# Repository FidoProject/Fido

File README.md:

# Creative Cloud for PlayOnLinux

**This script currently does not work, see [issue #52](https://github.com/corbindavenport/creative-cloud-linux/issues/52) for more details.**

This is an install script for [Adobe Creative Cloud](https://www.adobe.com/creativecloud.html), designed to be used with [PlayOnLinux](https://www.playonlinux.com). The script sets up the Adobe Creative Cloud desktop program, which can be used to install and update Photoshop, Lightroom, Dreamweaver, Illustrator, and other apps.

Only Photoshop CC, Bridge CC, Lightroom 5, and the Creative Cloud manager have been extensively tested. The newest Lightroom CC app is not supported right now. File syncing currently [does not work](https://github.com/corbindavenport/creative-cloud-linux/issues/29).

A (free) Adobe ID is required. Most Adobe applications require [a paid subscription](https://www.adobe.com/creativecloud/plans.html).

## How to use this script

1. Download PlayOnLinux from your distribution's package manager (e.g. Ubuntu Software Center) or from [the PlayOnLinux website](https://www.playonlinux.com/en/download.html)
2. Save the [install script](https://raw.githubusercontent.com/corbindavenport/creative-cloud-linux/master/creativecloud.sh) to your computer
3. Open PlayOnLinux, go to Tools > Run a local script
4. Select the install script you just downloaded

After the setup process is finished, you can open `Adobe Creative Cloud` from PlayOnLinux to download and install the apps you need. After you download an app, you can add a PlayOnLinux shortcut for it by clicking Adobe Application Manager in the app list, clicking `Configure`, and clicking `Make a new shortcut from this virtual drive`. Then look for the app you need, like Photoshop.exe, and add it.

**Tip:** Tooltips in Photoshop might not disappear automatically. You can turn off tooltips completely by going to `Edit > Preferences > Tools` and un-checking the `Show tooltips` box.

If the installer crashes, see the [Troubleshooting page](https://github.com/corbindavenport/creative-cloud-linux/wiki/Troubleshooting). If you still have issues, try [the classic script](https://github.com/corbindavenport/creative-cloud-linux/tree/classic).

---------------------------------------

    This program is free software: you can redistribute it and/or modify
    it under the terms of the GNU General Public License as published by
    the Free Software Foundation, either version 3 of the License, or
    (at your option) any later version.

    This program is distributed in the hope that it will be useful,
    but WITHOUT ANY WARRANTY; without even the implied warranty of
    MERCHANTABILITY or FITNESS FOR A PARTICULAR PURPOSE.  See the
    GNU General Public License for more details.

    You should have received a copy of the GNU General Public License
    along with this program.  If not, see <http://www.gnu.org/licenses/>.

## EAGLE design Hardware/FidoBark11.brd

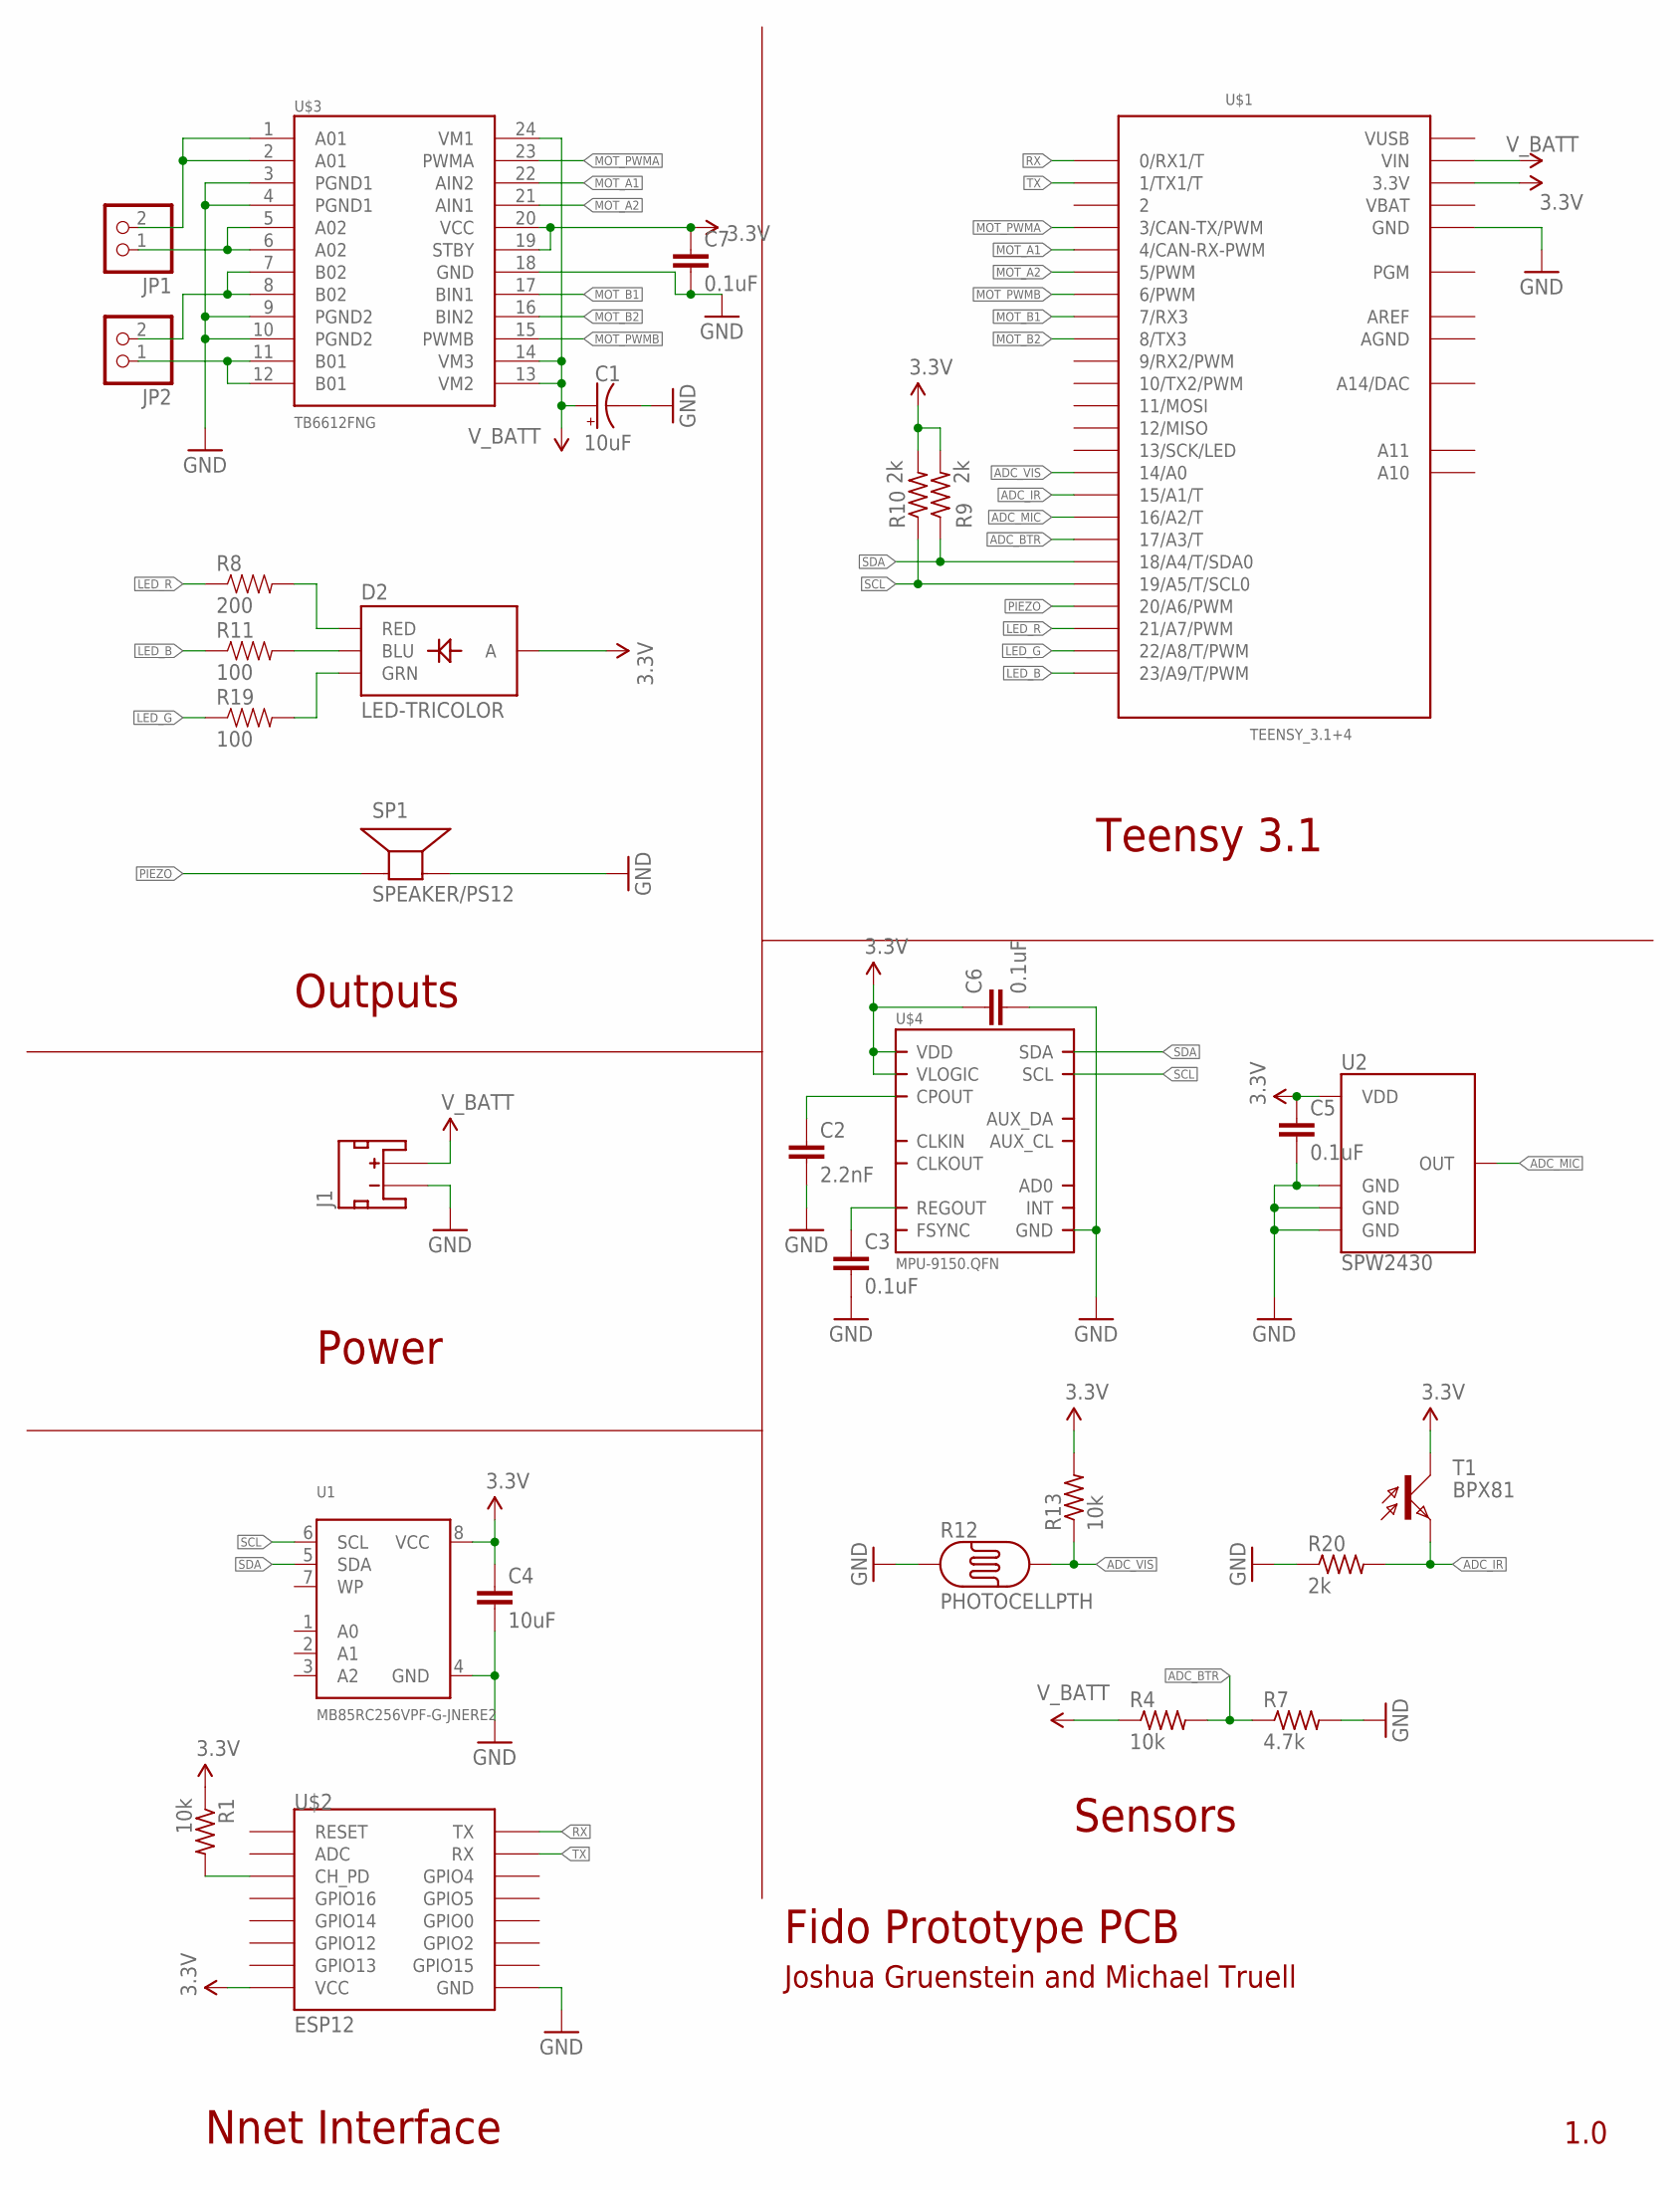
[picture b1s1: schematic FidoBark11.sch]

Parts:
C1: 10uF; EIA3216
C2: 2.2nF; C0603
C3, C5, C6, C7: 0.1uF; C0603
C4: 10uF; 0603-CAP
D2: LED-TRICOLOR; LED-TRICOLOR-SMD
J1: JST_2MM_MALE; JST-2-SMD
JP1, JP2: PINHD-1X2; 1X02
R1, R4, R13: 10k; R0603
R7: 4.7k; R0603
R8: 200; 0402-RES
R9, R10, R20: 2k; R0603
R11, R19: 100; 0402-RES
R12: PHOTOCELLPTH; PHOTOCELL
SP1: SPEAKER/PS12; PS12
T1: BPX81
U1: MB85RC256VPF-G-JNERE2; SOIC8_208MIL
U2: SPW2430; ADMP401
U$1: TEENSY_3.1+4
U$2: ESP12
U$3: TB6612FNG; SSOP24
U$4: MPU-9150.QFN; QFN.24.4X4

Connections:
3.3V: C4.1, C5.1, C6.1, C7.1, D2.A, R1.1, R9.2, R10.2, R13.2, T1.C, U1.8 (VCC), U2.5 (VDD), U$1.3.3V, U$1.3.3V1 (3.3V), U$2.VCC, U$3.19 (STBY), U$3.20 (VCC), U$4.3 (VDD), U$4.8 (VLOGIC), U$4.13 (VDD)
ADC_BTR: R4.2, R7.1, U$1.17/A3 (17/A3/T)
ADC_IR: R20.2, T1.E, U$1.15/A1 (15/A1/T)
ADC_MIC: U2.1 (OUT), U$1.16/A2 (16/A2/T)
ADC_VIS: R12.2, R13.1, U$1.14/A0
AGND: U$1.AGND
AREF: U$1.AREF
BLU: D2.B (BLU), R11.2
GND: C1.C (-), C2.2, C3.2, C4.2, C5.2, C6.2, C7.2, J1.1 (-), R7.2, R12.1, R20.1, SP1.P$2 (-), U1.4 (GND), U2.2 (GND), U2.4 (GND), U2.6 (GND), U$1.GND, U$1.GND1 (GND), U$2.GND, U$3.3 (PGND1), U$3.4 (PGND1), U$3.9 (PGND2), U$3.10 (PGND2), U$3.18 (GND), U$4.15 (GND), U$4.17 (GND), U$4.18 (GND)
GRN: D2.G (GRN), R19.2
LED_B: R11.1, U$1.23/A9 (23/A9/T/PWM)
LED_G: R19.1, U$1.22/A8 (22/A8/T/PWM)
LED_R: R8.1, U$1.21/A7 (21/A7/PWM)
MOT_A1: U$1.4 (4/CAN-RX-PWM), U$3.22 (AIN2)
MOT_A2: U$1.5 (5/PWM), U$3.21 (AIN1)
MOT_B1: U$1.7 (7/RX3), U$3.17 (BIN1)
MOT_B2: U$1.8 (8/TX3), U$3.16 (BIN2)
MOT_PWMA: U$1.3 (3/CAN-TX/PWM), U$3.23 (PWMA)
MOT_PWMB: U$1.6 (6/PWM), U$3.15 (PWMB)
unnamed: JP1.2, U$3.1 (A01), U$3.2 (A01)
unnamed: R1.2, U$2.CH_PD
unnamed: JP1.1, U$3.5 (A02), U$3.6 (A02)
unnamed: JP2.2, U$3.7 (B02), U$3.8 (B02)
unnamed: JP2.1, U$3.11 (B01), U$3.12 (B01)
unnamed: C3.1, U$4.10 (REGOUT)
unnamed: C2.1, U$4.20 (CPOUT)
PIEZO: SP1.P$1 (+), U$1.20/A6 (20/A6/PWM)
RED: D2.R (RED), R8.2
RX: U$1.0 (0/RX1/T), U$2.TX
SCL: R10.1, U1.6 (SCL), U$1.19/A5 (19/A5/T/SCL0), U$4.23 (SCL)
SDA: R9.1, U1.5 (SDA), U$1.18/A4 (18/A4/T/SDA0), U$4.24 (SDA)
TX: U$1.1 (1/TX1/T), U$2.RX
VBAT: U$1.VBAT
VUSB: U$1.VUSB
V_BATT: C1.A (+), J1.2 (+), R4.1, U$1.VIN, U$3.13 (VM2), U$3.14 (VM3), U$3.24 (VM1)

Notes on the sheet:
Sensors
Teensy 3.1
Fido Prototype PCB
Joshua Gruenstein and Michael Truell
1.0
Nnet Interface
Outputs
Power

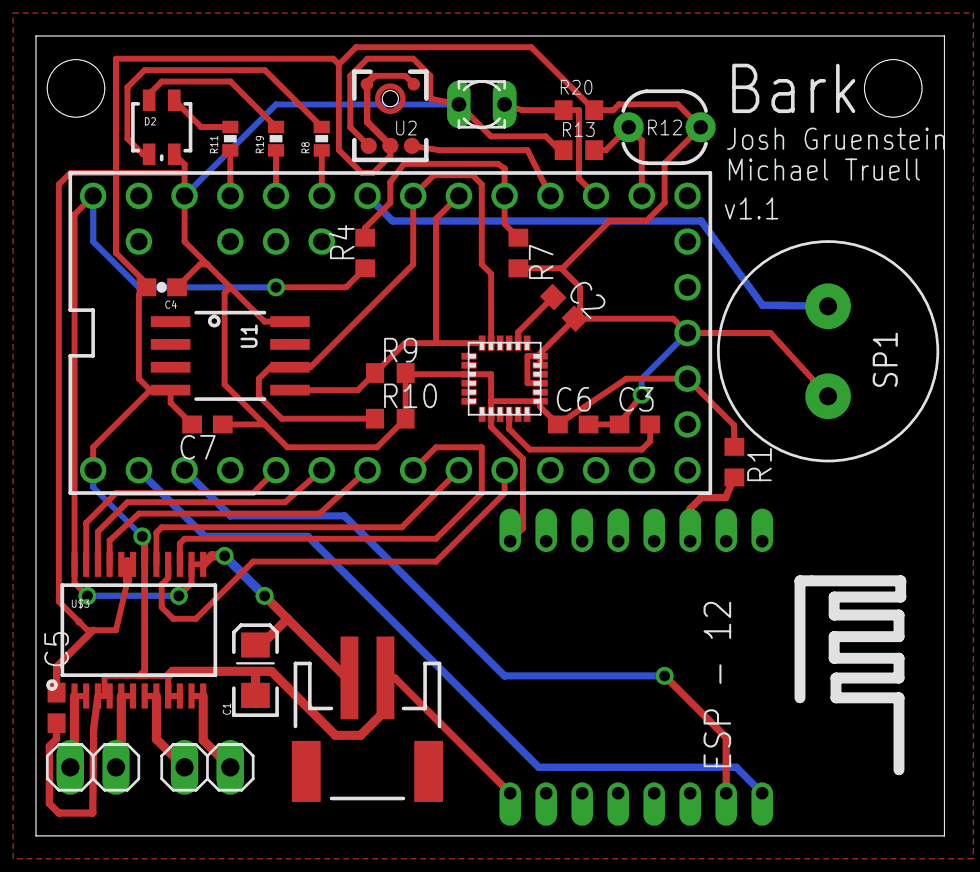
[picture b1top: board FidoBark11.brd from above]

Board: 2 copper layers, 50.5 x 44.4 mm, 30 parts (0 on the bottom side), 31 nets.

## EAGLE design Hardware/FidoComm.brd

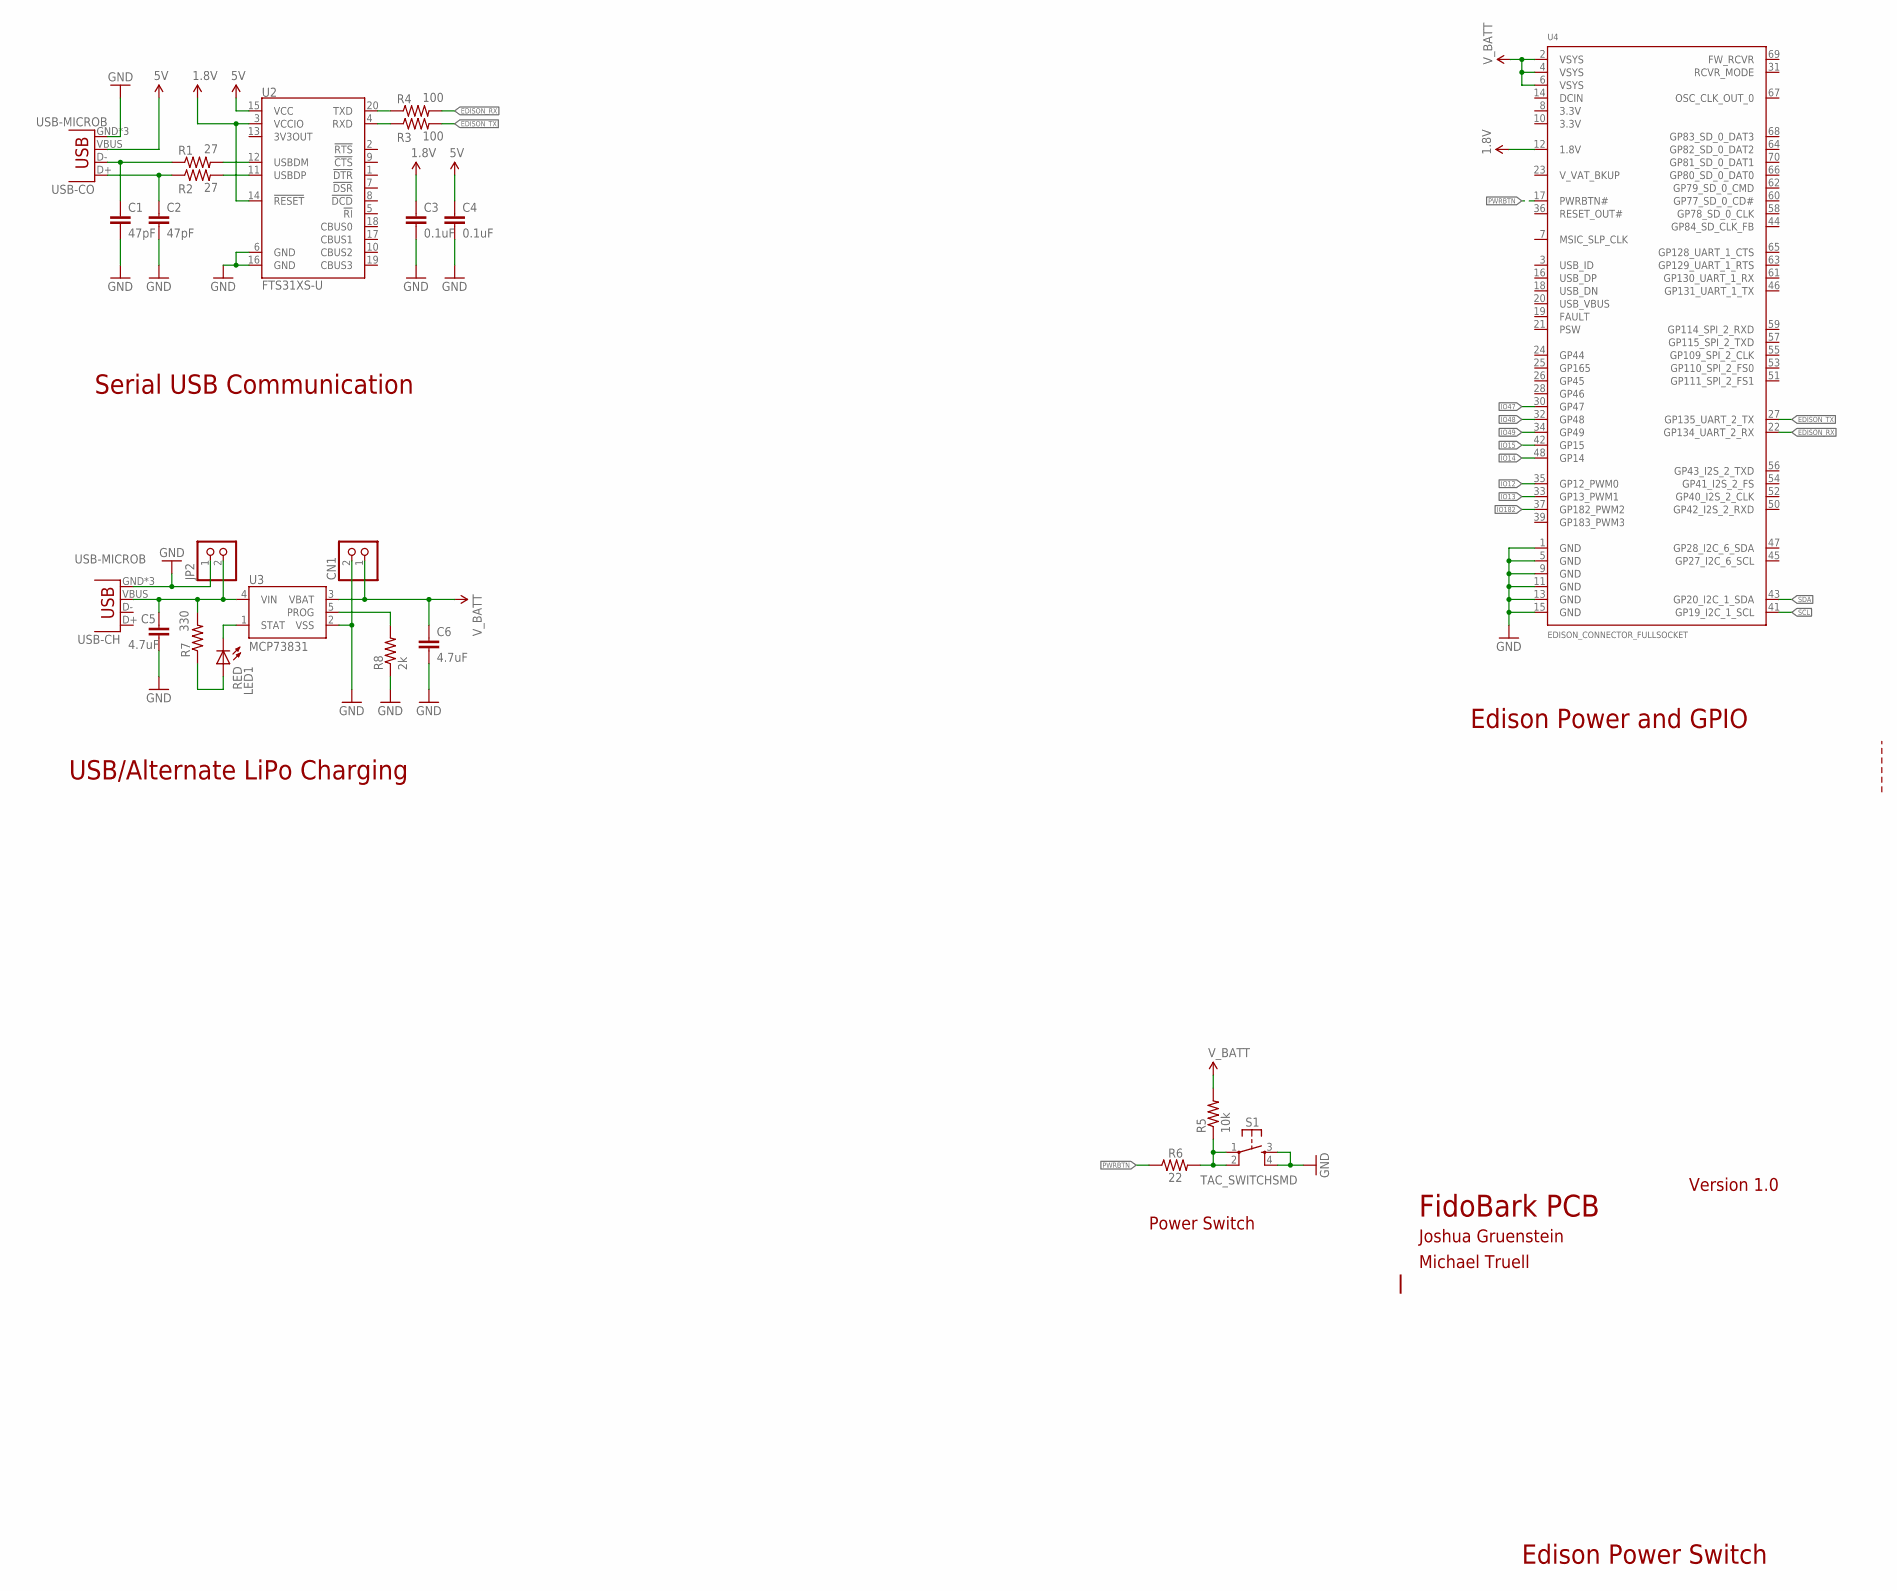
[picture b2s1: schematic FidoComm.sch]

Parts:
C1, C2: 47pF; 0603-CAP
C3, C4: 0.1uF; 0603-CAP
C5, C6: 4.7uF; 0603-CAP
CN1: JST_2PIN-SMT-RA; JST-PH-2-SMT-RA
JP2: PINHD-1X2; 1X02
LED1: RED; CHIP-LED0603
R1, R2: 27; R0603
R3, R4: 100; R0603
R5: 10k; R0603
R6: 22; R0603
R7: 330; R0603
R8: 2k; R0603
S1: TAC_SWITCHSMD; TACTILE-SWITCH-SMD
U2: FTS31XS-U; SSOP20_L
U3: MCP73831; SOT23-5
U4: EDISON_CONNECTOR_FULLSOCKET; DF40-XC-(X.X)-70DS-0.4V(51)
USB-CH: USB-MICROB
USB-CO: USB-MICROB

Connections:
1.8V: C3.1, U2.3 (VCCIO), U2.14 (!RESET), U4.12 (1.8V)
5V: C4.1, U2.15 (VCC), USB-CO.VBUS
EDISON_RX: R4.2, U4.22 (GP134_UART_2_RX)
EDISON_TX: R3.2, U4.27 (GP135_UART_2_TX)
GND: C1.2, C2.2, C3.2, C4.2, C5.2, C6.2, CN1.2 (1), JP2.1, R8.1, S1.3, S1.4, U2.6 (GND), U2.16 (GND), U3.2 (VSS), U4.1 (GND), U4.5 (GND), U4.9 (GND), U4.11 (GND), U4.13 (GND), U4.15 (GND), USB-CH.GND, USB-CH.MT1 (GND), USB-CH.MT2 (GND), USB-CO.GND, USB-CO.MT1 (GND), USB-CO.MT2 (GND)
IO12: U4.35 (GP12_PWM0)
IO13: U4.33 (GP13_PWM1)
IO14: U4.48 (GP14)
IO15: U4.42 (GP15)
IO47: U4.30 (GP47)
IO48: U4.32 (GP48)
IO49: U4.34 (GP49)
IO182: U4.37 (GP182_PWM2)
unnamed: R2.2, U2.11 (USBDP)
unnamed: R1.2, U2.12 (USBDM)
unnamed: R3.1, U2.4 (RXD)
unnamed: C2.1, R2.1, USB-CO.D+
unnamed: C1.1, R1.1, USB-CO.D-
unnamed: R4.1, U2.20 (TXD)
unnamed: R5.1, R6.2, S1.1, S1.2
unnamed: LED1.A, R7.1
unnamed: LED1.C, U3.1 (STAT)
unnamed: R8.2, U3.5 (PROG)
unnamed: C5.1, JP2.2, R7.2, U3.4 (VIN), USB-CH.VBUS
PWRBTN: R6.1, U4.17 (PWRBTN#)
SCL: U4.41 (GP19_I2C_1_SCL)
SDA: U4.43 (GP20_I2C_1_SDA)
V_BATT: C6.1, CN1.1 (2), R5.2, U3.3 (VBAT), U4.2 (VSYS), U4.4 (VSYS), U4.6 (VSYS)

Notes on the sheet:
Serial USB Communication
USB/Alternate LiPo Charging
Edison Power and GPIO
Edison Power Switch
Power Switch
FidoBark PCB
Joshua Gruenstein
Michael Truell
Version 1.0

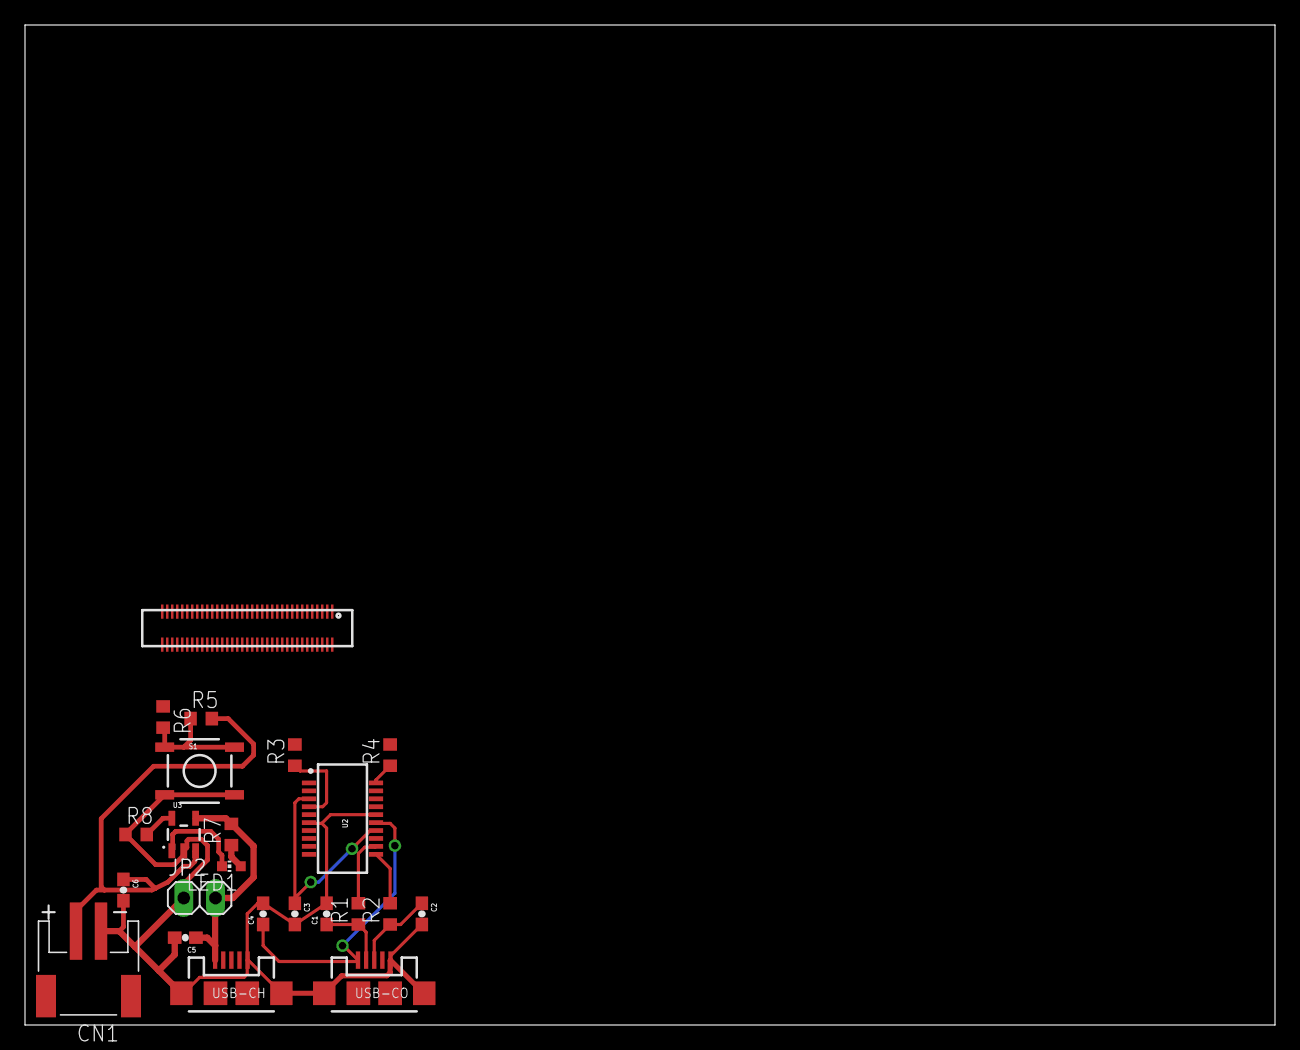
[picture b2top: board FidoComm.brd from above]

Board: 2 copper layers, 100.0 x 80.0 mm, 23 parts (0 on the bottom side), 18 nets.

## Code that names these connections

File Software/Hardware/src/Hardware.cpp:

#include "Hardware.h"

#define BUZZ_PIN 14
#define LED_R_PIN 20
#define LED_G_PIN 0
#define LED_B_PIN 21

Hardware::Hardware() {
	/// init IMU
	imu = new LSM9DS0(0x6B, 0x1D);
	imu->begin();

	/// init motors
	motors.standby(false);

	/// init adc
    adc_i2c = new mraa::I2c(1);
    adc = new ads1015(adc_i2c, 0x48);
    adc->setRange(_4_096V);

    /// init buzzer
    //buzz = new upm::Buzzer(BUZZ_PIN);

    /// init RGB strip
    pwmR = new mraa::Pwm(LED_R_PIN);
    pwmG = new mraa::Pwm(LED_G_PIN);
	pwmB = new mraa::Pwm(LED_B_PIN);
	pwmR->enable(true);
	pwmG->enable(true);
	pwmB->enable(true);
}

TDVect Hardware::getGyro() {
	TDVect returnVect;
	imu->readGyro();
	returnVect.xComp = imu->calcGyro(imu->gx);
	returnVect.yComp = imu->calcGyro(imu->gy);
	returnVect.zComp = imu->calcGyro(imu->gz);
	return returnVect;
}

TDVect Hardware::getAccel() {
	TDVect returnVect;
	imu->readAccel();
	returnVect.xComp = imu->calcAccel(imu->ax);
	returnVect.yComp = imu->calcAccel(imu->ax);
	returnVect.zComp = imu->calcAccel(imu->ax);
	return returnVect;
}

TDVect Hardware::getCompass() {
	TDVect returnVect;
	imu->readMag();
	returnVect.xComp = imu->calcMag(imu->mx);
	returnVect.yComp = imu->calcMag(imu->my);
	returnVect.zComp = imu->calcMag(imu->mz);
	return returnVect;
}

void Hardware::setMotors(int motorOne, int motorTwo) {
	motors.shortBrake(motorOne==0,motorTwo==0);
	double scaleOne = motorOne/-100.0;
	double scaleTwo = motorTwo/-100.0;
	motors.diffDrive(scaleOne,scaleTwo);
}

void Hardware::chirp(double volume, int frequency, int time) {
	//buzz->setVolume(volume);
	//buzz->playSound(frequency,time);
}

double Hardware::getVis() {
	return adc->getRawResult(3)/2047.0;
}

double Hardware::getMicrophone() {
	return adc->getRawResult(2)/2047.0;
}

double Hardware::getLoudness(int samples) {
	double x = 0;
	for (int i=0; i<samples; i++) {
		double y = getMicrophone();
		x = (y>x)?y:x;
	} return x;
}

double Hardware::getIR() {
	return adc->getRawResult(1)/2047.0;
}

void Hardware::setLed(double r, double g, double b) {
	pwmR->write(r);
	pwmG->write(g);
	pwmB->write(b);
}

double Hardware::getTemperature() {
	imu->readTemp();
	return imu->temperature/4096.0;
}

int Hardware::safeClose() {
	setMotors(0,0);
	//buzz->stopSound();
	setLed(0,0,0);

	usleep(100000);
}

Hardware::~Hardware() {
	safeClose();

	//delete buzz;
	delete adc_i2c;
	delete adc;
	delete imu;
	delete pwmR;
	delete pwmG;
	delete pwmB;
}

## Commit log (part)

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2016-03-17 Fix compilation errors from pre-NYCSEF rush
2016-03-17 Took out documentation folder
2016-03-18 Stay still task
2016-03-18 Took out little line
2016-03-18 Took out Staystill task
2016-03-18 Remove PastNN
2016-03-18 Added newline to feedback
2016-03-18 Added actual operator overload
2016-03-18 Doxygen commenting for Backpropagation
2016-03-18 Doxygen config
2016-03-18 Change logo
2016-03-18 Undo dumb thing
2016-03-18 Convert all indentation to tabs
2016-03-18 Revert "Added newline to feedback"
    This reverts commit 1449c351772201090c1ead32b0148611eeaf2abf.
2016-03-18 Fix double comment
2016-03-18 Took out typo in @flyinggraysons README change
2016-03-18 Cut down install instructions
2016-03-18 Clarified Unix/Windows instructions
2016-03-18 Fix @flyinggraysons duplicate comments
2016-03-18 Took out fcc compile instruction
2016-03-19 Linear output activation function
2016-03-19 Put example code in repo
2016-03-19 Add newline to feedback
2016-03-19 accidentally made learning iters huge
2016-03-19 Make SFML required
2016-03-19 Require SFML
2016-03-19 Docs for Backpropagation.cpp
2016-03-19 Windows install script
2016-03-19 Windows bat file in readme
2016-03-19 Allow without simulator
2016-03-20 Learner class
2016-03-20 Remake of Qlearn
2016-03-20 Move to RL namespance
2016-03-20 Deleted unecessary binary
2016-03-20 Move Task
2016-03-20 Learner
2016-03-20 One robot class
2016-03-20 Removed foo exec
2016-03-21 Add catch and makefile for tests
2016-03-21 update for header name change
2016-03-21 Added travis cl
2016-03-21 Added more travis fixes
2016-03-21 maybe travis will work now
2016-03-21 dude what is this
2016-03-21 add unit test to travis
2016-03-21 maybe this will work
2016-03-21 Thanks google
2016-03-21 used += in makefiles
2016-03-21 fFix chmod
2016-03-21 add SFML to travis
2016-03-21 Revert "delete useless stuff"
    This reverts commit 3e625e54d2080f07729b251f584389cea31da0de.
2016-03-21 Add activation check
2016-03-21 Add unit test readme
2016-03-21 Fixed unit tests
2016-03-21 Lowered double rounding error threshold
2016-03-21 Figuring out travis dir structure
2016-03-21 Fix to travis yml
2016-03-21 Another possible fix to travis config
2016-03-21 Yet another fix
2016-03-21 Another one
2016-03-21 No SFML fixes
2016-03-21 Compile without sfml if right files are deleted
2016-03-21 noSFML makefile fix
2016-03-21 Get rid of typo in info echo
2016-03-21 Fix to g++ config
2016-03-21 If statements
2016-03-21 Travis status in README
2016-03-21 Un-catch the repo
2016-03-21 Make everything .hpp
2016-03-21 Use make clean instead of rm
2016-03-21 Add test file to gitignore
2016-03-21 Revert "Make everything .hpp"
    This reverts commit 4e120b43f4a845b041b5c3bbfd8711f1ca7af6a8.
2016-03-21 Revert "Delete .gitattributes"
    This reverts commit 83024fc889f3f8cb689ca7a6d814600b84bc4f2e.
2016-03-21 remove travis syntax error
2016-03-21 Took out clang
2016-03-21 Put g++ flags back in
2016-03-21 Fix Issue #18
2016-03-21 Backpropagation doesnt need you to specify derived functions
2016-03-21 Revert "Fix Issue #18"
    This reverts commit 11a2518b9a24f7c8735f03f206a5d243210a4472.
2016-03-21 Testing something for travis
2016-03-22 Activation function documentation
2016-03-22 Remove driver for time being
2016-03-22 Add SFML v2.0
2016-03-22 Accidentally added valgrind twice
2016-03-22 switched to parallel builds
2016-03-22 fix env vars
2016-03-22 Add valgrind testing for examples
2016-03-22 Revert "Add valgrind testing for examples"
    This reverts commit 31b694bf7a4e2aac9b9b9ada3c18f51567ddf99f.
2016-03-22 Revert "Add example directory"
    This reverts commit 6753899bf08bb9868500cd380a9cb2a9c461987b.
2016-03-22 Remove unecessary forward dec
2016-03-23 layer documentation
2016-03-23 learner documentation
2016-03-23 lsinterpolator documentation
2016-03-23 neuron documentation
2016-03-23 Added mainpage
2016-03-24 Rename to documentation
2016-03-24 Remove Robot and Task (They are unnecessary)
2016-03-24 Throw error on impossible nn conditions
2016-03-24 Fix typo bug
2016-03-24 Took out instructions
2016-03-25 Fixed formatting error
2016-03-25 Add back propagation test
2016-03-25 Re-add genetic algorithms
    fixes #9
2016-03-25 Add specific unit test control to runtests.sh
2016-03-25 Add error quit to install.sh
2016-03-25 Optimize travis
2016-03-25 Changed network test according to filestorage changes
2016-03-25 Require storage from all trainers
2016-03-25 Move gradient computation to NeuralNet
2016-03-25 Removed unneeded assets
2016-03-26 Remove getting Started
2016-03-26 Move genetic algs
2016-03-26 Update tests
2016-03-26 Added line following sensor
2016-03-26 Fix to nn unit test
2016-03-26 link SFML in unit test makefile
2016-03-26 Line following unit tests
2016-03-26 Changes to WireFitQLearn
2016-03-26 Make consts static
2016-03-26 Z X sensor
2016-03-26 Require travis
2016-03-26 Gitignore unneccessary testing files
2016-03-26 Gitignore temp folder
2016-03-26 Travis valgrind fix
2016-03-26 Add better no SFML support
2016-03-26 Get rid of file deletion for tests
    bc truell
2016-03-26 way to make it mandatory
2016-03-26 Truell you did some weird stuff
2016-03-27 Edited Henry's backprop tests
2016-03-27 Gotta create temp folder in unit test runner
2016-03-27 Move everything
2016-03-27 Got rid of dumb compiler
2016-03-27 Update stray files
2016-03-27 and there we go
2016-03-27 Add better makefile instructions
2016-03-27 Add travis support
2016-03-27 Fix for travis
2016-03-27 rename includes to include
2016-03-27 Fix .cpp's for this
2016-03-27 update travis
2016-03-27 add fido.h
2016-03-27 Add SFML support
2016-03-27 Finally
2016-03-27 hopefully travis will work now
2016-03-27 src vs software renaming
2016-03-27 Changes to defaults
2016-03-27 Consolidated simulator to one folder
2016-03-27 Fix tests
2016-03-27 Change make and config to new changes
2016-03-27 exclude tests folder from doxygen
2016-03-27 Fixed simulator test
2016-03-27 Josh's buggy kiwi drive
2016-03-27 Fido control system implementation
2016-03-27 Added documentation link
2016-03-27 Add uninstall option to makefile
2016-03-28 Take out history sampling temporairly
2016-03-28 Fixes to discrete
2016-03-28 Automaticly randomize weights on init
2016-03-28 Fix Fido.h file
2016-03-28 Fixed history sampling
2016-03-28 History Sampling Change (pick histories with very different initial states)
2016-03-30 Take out travis badge
2016-03-30 Change to simulator test
2016-04-07 Makefile copy include recursively
2016-04-09 Fixed kiwi test
2016-04-10 Ran through gcc-linter
2016-04-10 Revert "Remove Interpolator's getInterpolatorFromFile method"
    This reverts commit 69c9f6edd69cf9c9169cd450dc777d1ab459f388.
2016-04-10 Further linting
2016-04-10 Add travis badge
2016-04-10 Made the Travis Badge a link to our Travis page
2016-04-17 Moved Layer to class
2016-04-17 Added proper imports and applied fixes to Line construct
2016-04-20 Pruning
2016-04-20 Fix to pruning test
2016-04-21 Genetic algorithm documentation
2016-04-21 Genetic algo improvements
2016-04-21 Genetic algorithm example
2016-04-22 Add getting of best network to GA example
2016-04-22 GA test
2016-04-22 Take out annoying cout in GA
2016-04-22 Decouple history sampling from WireFitQLearn
2016-04-22 switch fido control system to pruning
2016-04-22 Improvements to pruner
2016-04-23 All documentation except for Simulator
2016-04-23 Tan sigmoid derivative
2016-04-23 Adadelta test
2016-04-23 Fixes to adadelta documentation
2016-04-23 Make adadelta test quicker
2016-04-23 Tweak adadelta params
2016-04-23 Tiny Adadelta edits
2016-04-24 Moar examples
2016-04-24 Small fix to rl example
2016-04-24 Exploration optimization working nicely
2016-04-24 another good place
2016-04-24 No need for another constant
2016-04-24 Caps
2016-04-24 Pruning safety
2016-04-28 Take out untested windows install file
2016-04-28 Take out simulator
2016-04-28 Take out storage
2016-04-28 Take out pruning and simulator tests
2016-04-28 Apply stash
2016-04-28 Revert
2016-04-28 Revert "Take out storage"
    This reverts commit f98ee1c6438443a69d0fac035d4d61cbbc7bc5d7.
    Conflicts:
    src/Adadelta.cpp
2016-04-28 Revert "Take out pruner"
    This reverts commit e17c261c85306de96cec0cd7854c296015f15371.
    Conflicts:
    src/Pruner.cpp
2016-04-28 Lightweight
2016-04-29 Remove doxygen config
2016-04-29 Rm example doxygen
2016-04-29 Add Trainer serializations
2016-04-29 Fix to simulator loading of resources
2016-04-29 Start work on Learner serialization
2016-04-29 Decouple pruning
2016-04-29 "SGD superclass trainer"
2016-04-29 Fix build and test error
2016-04-29 Backpropagation to SGDTriner
2016-04-29 Move Adadelta to SGDTrainer
2016-04-29 Qlearn non trainer specific
2016-04-29 Qlearn test
2016-04-30 Dynamic resizing of neural nets
2016-04-30 Tweaks to network resizing
2016-04-30 Stuff working
2016-04-30 Clenup
2016-04-30 Line follow holo good
2016-04-30 Optimizations on the pi
2016-05-01 Make pruning and reinforcement tests more reliable
2016-05-01 Sample most different histories
2016-05-01 SGD on history sampling (less latency)
2016-05-01 Qlearn with no history sampling
2016-05-01 drive to point holo works
2016-05-01 DRIVE HOLO WORKS
2016-05-01 witchcraft
2016-05-02 Revert "witchcraft"
    This reverts commit f13d9ff7ce1528bc9c2b48795cccefbaa8648356.
2016-05-02 Add trainer create
2016-05-03 Add travis coveralls support Also added extra capacity to the ./configure and Makefile to deal with GCOV
2016-05-03 Added coverall badge to README
2016-05-03 Fix typo
2016-05-03 Add conditional for coverall trigger
2016-05-03 Add correct flags to tests makefile
2016-05-03 Comment out travis lines that fail
2016-05-03 Didn't get commited properly
2016-05-03 Remove reinforcement test
2016-05-03 Switched flags
2016-05-03 Coverall Fix (Hopefully)
2016-05-03 Switch install order
2016-05-04 New coveralls method
2016-05-04 Change default args
2016-05-04 Improve the ./configure
2016-05-04 Fix confusion
2016-05-04 Add export one liner
2016-05-04 Go back to old coveralls technique
2016-05-04 Re-add bin dir
2016-05-05 Lower resizing latency
2016-05-10 Badges everywhere
2016-05-10 Badges everywhere (#46)
2016-05-10 Take out coveralls badge until full integration
2016-05-10 Ignore tests, docs, and travis on release
2016-05-10 Remove simulator from master
2016-05-10 Takeout configure from Travis
2016-05-10 Run simlator test
2016-05-10 Take out simulator test
2016-05-10 Run simulator test
2016-05-10 Typo fix (thanks @vaedprasad)
2016-05-11 Grammar Tweaks
2016-05-12 Fix GCOV flag not being added
2016-05-20 Run all unit tests
2016-05-20 More Q learn trials
2016-05-20 Finish implementing approximate compare for network test
2016-05-20 Added assert and took out exceptions
2016-05-21 Changed SGDTrainer::initFromStream to be void
2016-05-21 Fixed some asserts and indenting, and took out more false boolean functions
2016-05-21 Took out more false boolean functions
2016-05-21 Make pruner test more reliable
2016-05-21 Take out q-learning boltzman log pollution
2016-05-21 Improve genetic and reinforcement reliability
2016-05-21 Fixed some bugs with asserts.
2016-05-21 Asserts and change of bool initFromStream functions to voids. (#57)
    * Added assert and took out exceptions
    * Changed SGDTrainer::initFromStream to be void
    * Fixed some asserts and indenting, and took out more false boolean functions
    * Took out more false boolean functions
    * Fixed bad character
    * Fixed some bugs with asserts.
2016-05-21 Improve reinforcement test reliability
2016-05-26 Add slack integration
2016-06-01 Normalize identation in SGDTrainer.cpp (#59)
    Ha, thanks for doing this.
2016-06-01 Tabs to spaces
2016-06-01 Remove unnecessary test headers
2016-06-01 Revert "Remove unnecessary test headers"
    This reverts commit 1e2682218c35aabdc00f21fffe612a98f481172a.
2016-06-02 Style corrections
2016-06-02 Style corrections (#60)
2016-06-04 For loop corrections
2016-06-09 Update LICENSE
2016-06-09 update wirefit qlearn unit test
2016-06-09 Correct typos
2016-06-10 Pruning test more stable
2016-06-10 Compile fix to unit test
2016-06-10 Make reinforcement test more stable
2016-06-23 Take out valgrind
2016-10-03 Beta Status
2017-11-01 Revert "Remove simulator from master"
    This reverts commit 5435feb2364ee2ec1281825c52da6645ca6e0929.
2017-11-10 Temp Remove Travis
2017-11-18 Install SFML on travis
2019-07-08 Add files via upload
    UI

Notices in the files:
parts and their libraries:
SparkFun-Capacitors: Licensing: Creative Commons ShareAlike 4.0 International - https://creativecommons.org/licenses/by-sa/4.0
microbuilder: This work is placed in the public domain, and may be freely used for commercial and non-commercial work with the following conditions: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
